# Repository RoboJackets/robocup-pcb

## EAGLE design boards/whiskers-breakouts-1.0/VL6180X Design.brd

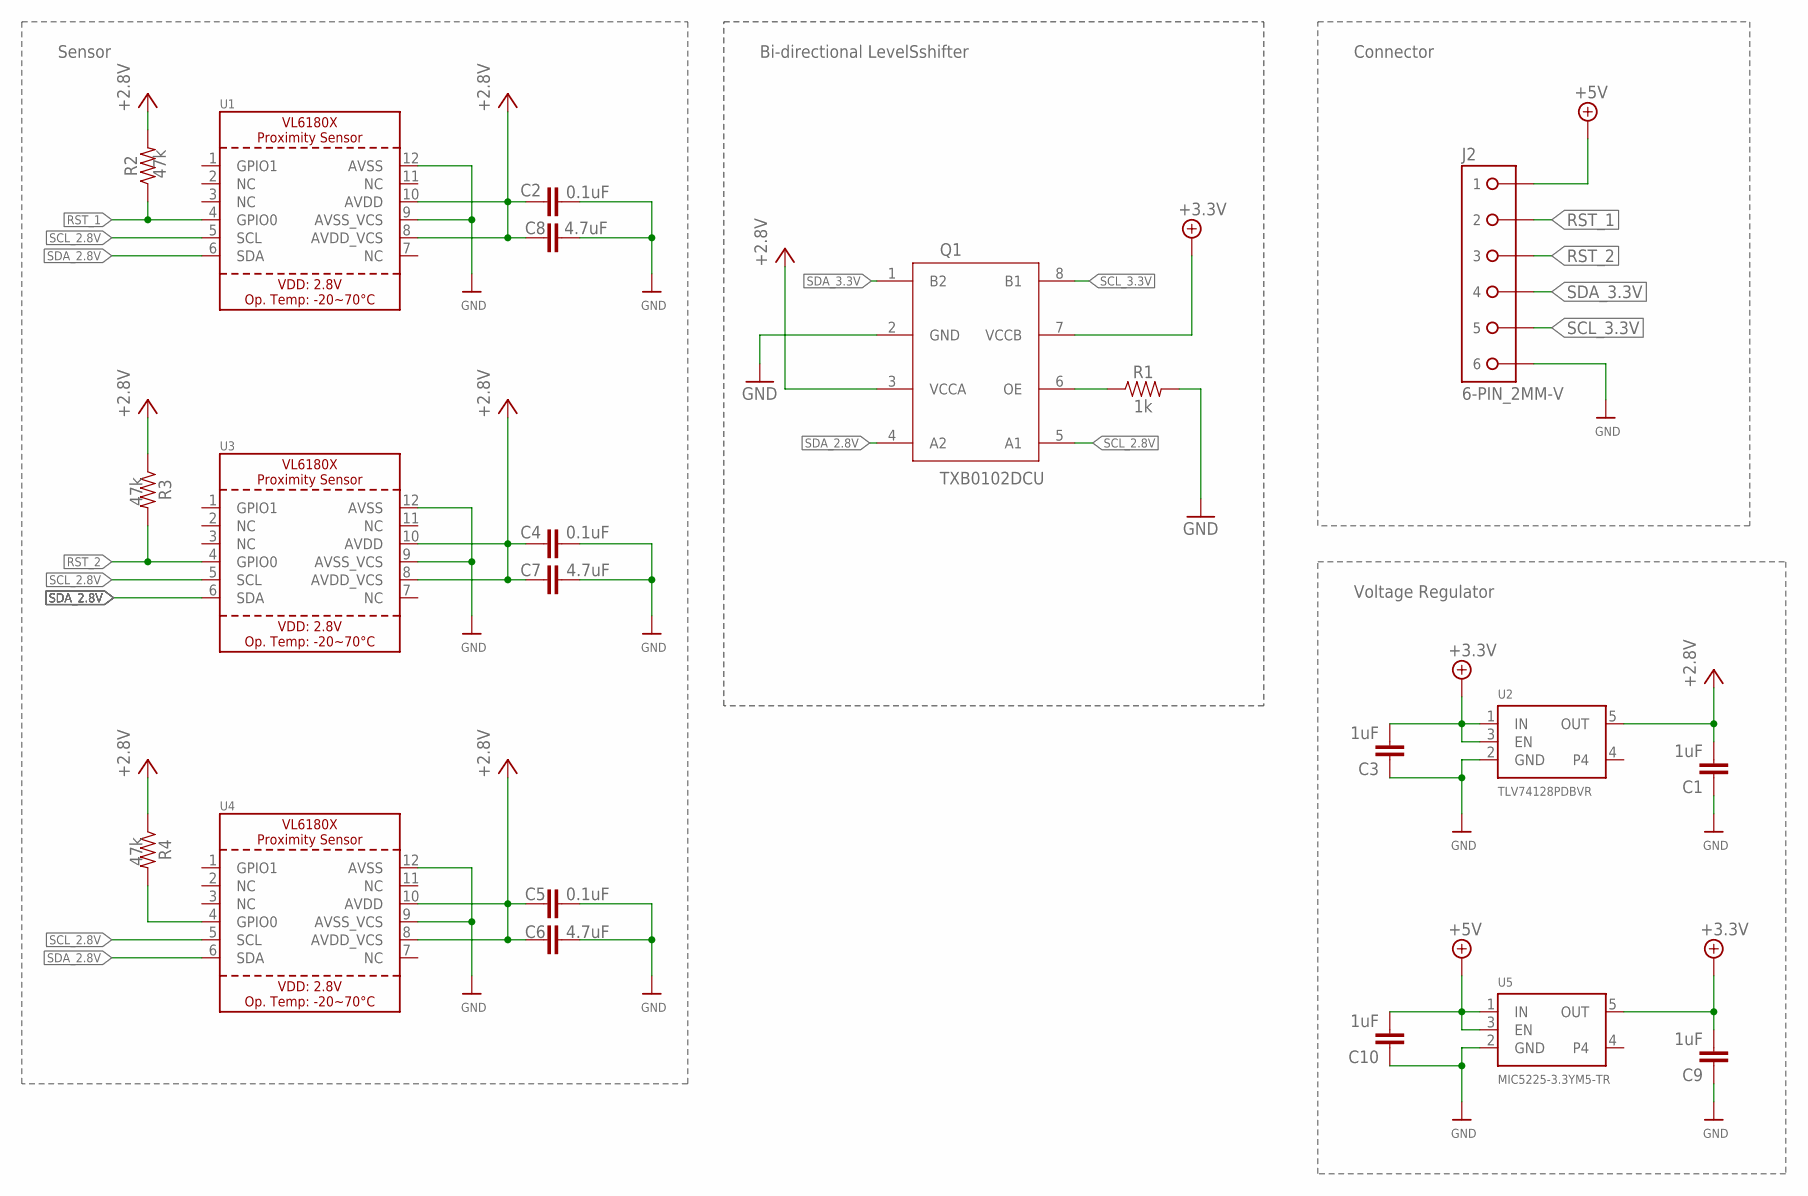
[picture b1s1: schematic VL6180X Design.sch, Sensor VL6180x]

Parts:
C1, C3, C9, C10: 1uF; 0603
C2, C4, C5: 0.1uF; 0603
C6, C7, C8: 4.7uF; 0603
J2: 6-PIN_2MM-V; 2MM-6-V
Q1: TXB0102DCU; VFSOP-8
R1: 1k; 0603
R2, R3, R4: 47k; 0603
U1, U3, U4: VL6180X; VL6180
U2: TLV74128PDBVR; SOT23-5
U5: MIC5225-3.3YM5-TR; SOT23-5

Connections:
+2.8V: C1.2, C2.1, C4.1, C5.1, C6.1, C7.1, C8.1, Q1.3 (VCCA), R2.2, R3.1, R4.1, U1.8 (AVDD_VCS), U1.10 (AVDD), U2.5 (OUT), U3.8 (AVDD_VCS), U3.10 (AVDD), U4.8 (AVDD_VCS), U4.10 (AVDD)
+3.3V: C3.2, C9.2, Q1.7 (VCCB), U2.1 (IN), U2.3 (EN), U5.5 (OUT)
+5V: C10.2, J2.1, U5.1 (IN), U5.3 (EN)
GND: C1.1, C2.2, C3.1, C4.2, C5.2, C6.2, C7.2, C8.2, C9.1, C10.1, J2.6, Q1.2 (GND), R1.2, U1.9 (AVSS_VCS), U1.12 (AVSS), U2.2 (GND), U3.9 (AVSS_VCS), U3.12 (AVSS), U4.9 (AVSS_VCS), U4.12 (AVSS), U5.2 (GND)
unnamed: Q1.6 (OE), R1.1
RST_1: J2.2, R2.1, U1.4 (GPIO0)
RST_2: J2.3, R3.2, U3.4 (GPIO0)
RST_3: R4.2, U4.4 (GPIO0)
SCL_2.8V: Q1.5 (A1), U1.5 (SCL), U3.5 (SCL), U4.5 (SCL)
SCL_3.3V: J2.5, Q1.8 (B1)
SDA_2.8V: Q1.4 (A2), U1.6 (SDA), U3.6 (SDA), U4.6 (SDA)
SDA_3.3V: J2.4, Q1.1 (B2)

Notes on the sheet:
Sensor
Connector
Bi-directional LevelSshifter
Voltage Regulator

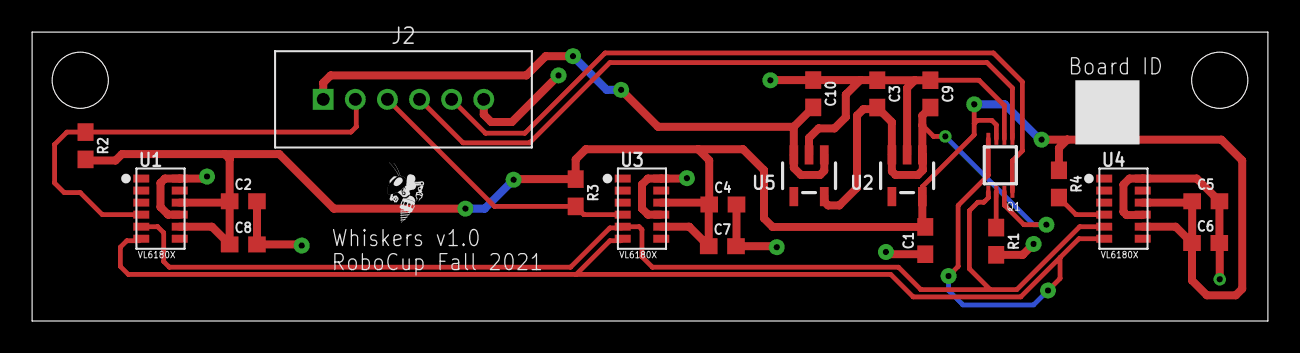
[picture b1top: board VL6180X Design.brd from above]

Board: 2 copper layers, 77.0 x 18.0 mm, 22 parts (0 on the bottom side), 12 nets.

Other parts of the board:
U$12: ROBOBUZZ_0.2X

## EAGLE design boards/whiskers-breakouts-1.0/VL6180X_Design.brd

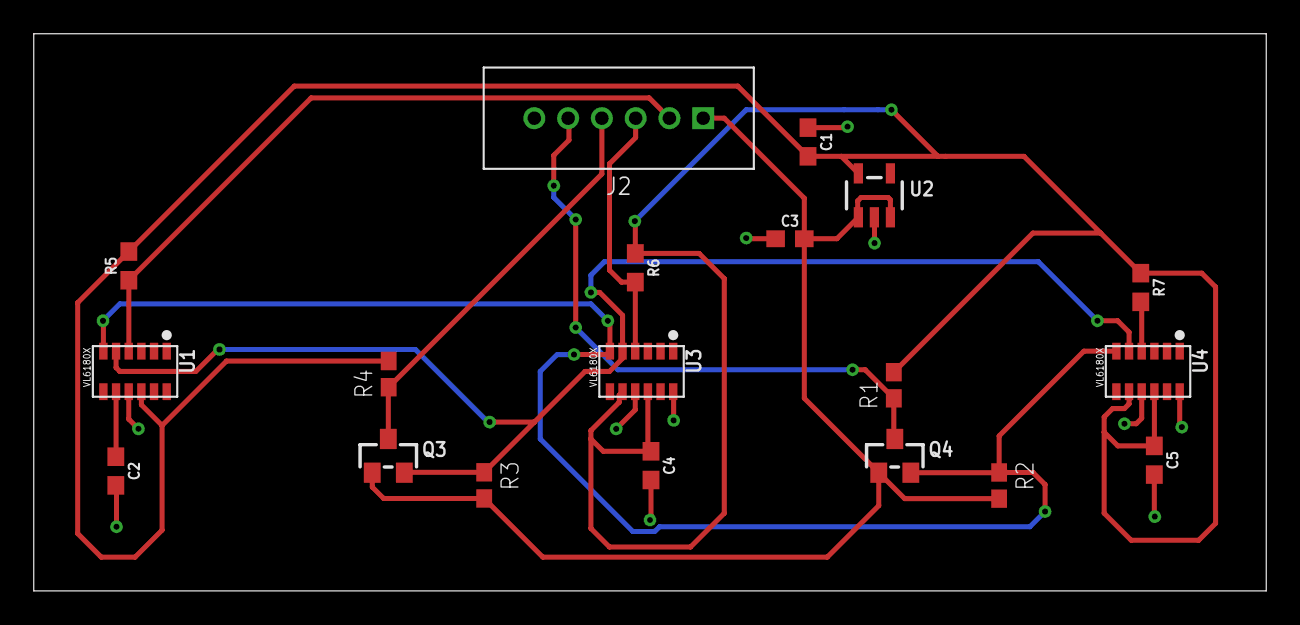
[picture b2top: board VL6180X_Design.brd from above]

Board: 2 copper layers, 73.0 x 33.0 mm, 19 parts (0 on the bottom side), 10 nets.

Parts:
C1, C3: 1uF; 0603
C2, C4, C5: 0.1uF; 0603
J2: 6-PIN_2MM-V; 2MM-6-V
Q3, Q4: BSS138; SOT23-WIDE
R1: 10k; R0603W
R2, R3, R4: 4.7k; R0603W
R5, R6, R7: 47k; 0603
U1, U3, U4: VL6180X; VL6180
U2: MIC5225_2.8V; SOT23-5

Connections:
+3.3V: C3.2, J2.1, Q3.1, Q4.1, R2.2, R3.2, U2.1, U2.3
GND: C1.1, C2.2, C3.1, C4.2, C5.2, J2.6, U1.9, U1.12, U2.2, U3.9, U3.12, U4.9, U4.12
RST_1: J2.2, R5.1, U1.4
RST_2: J2.3, R6.2, U3.4
RST_3: R7.2, U4.4
SCL_2.8V: Q3.2, R3.1, U1.5, U3.5, U4.5
SCL_3.3V: J2.4, Q3.3, R4.1
SDA_2.8V: Q4.2, R2.1, U1.6, U3.6, U4.6
SDA_3.3V: J2.5, Q4.3, R1.1
VCC: C1.2, C2.1, C4.1, C5.1, R1.2, R4.2, R5.2, R6.1, R7.1, U1.8, U1.10, U2.5, U3.8, U3.10, U4.8, U4.10

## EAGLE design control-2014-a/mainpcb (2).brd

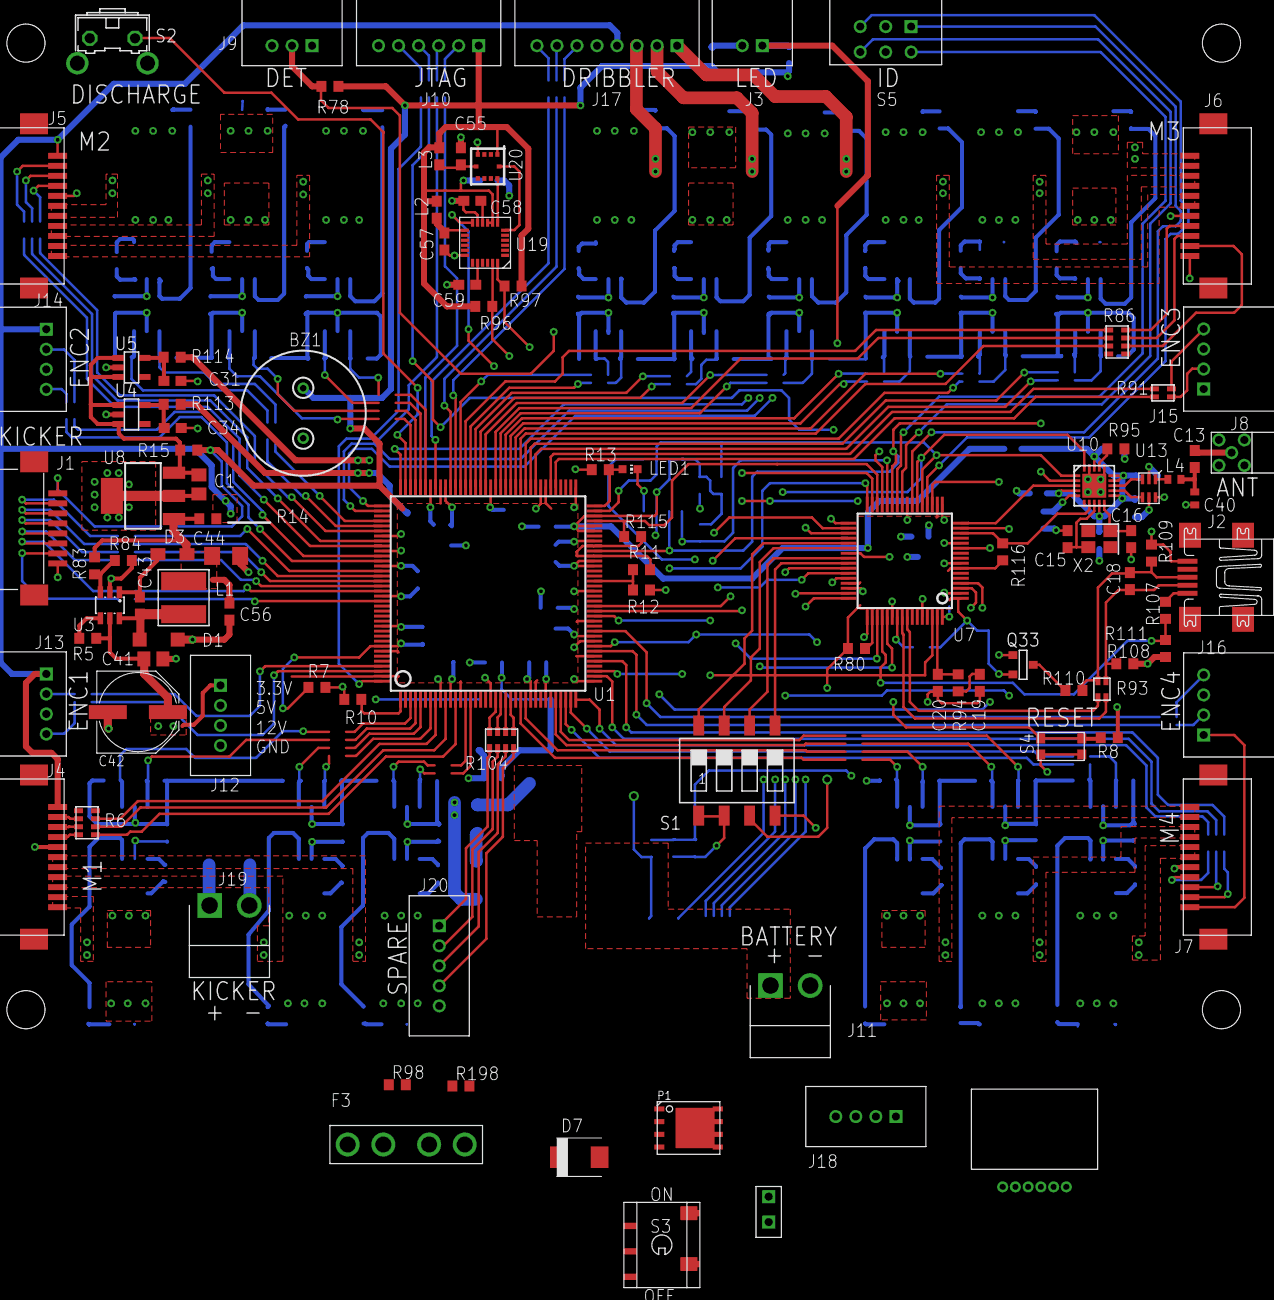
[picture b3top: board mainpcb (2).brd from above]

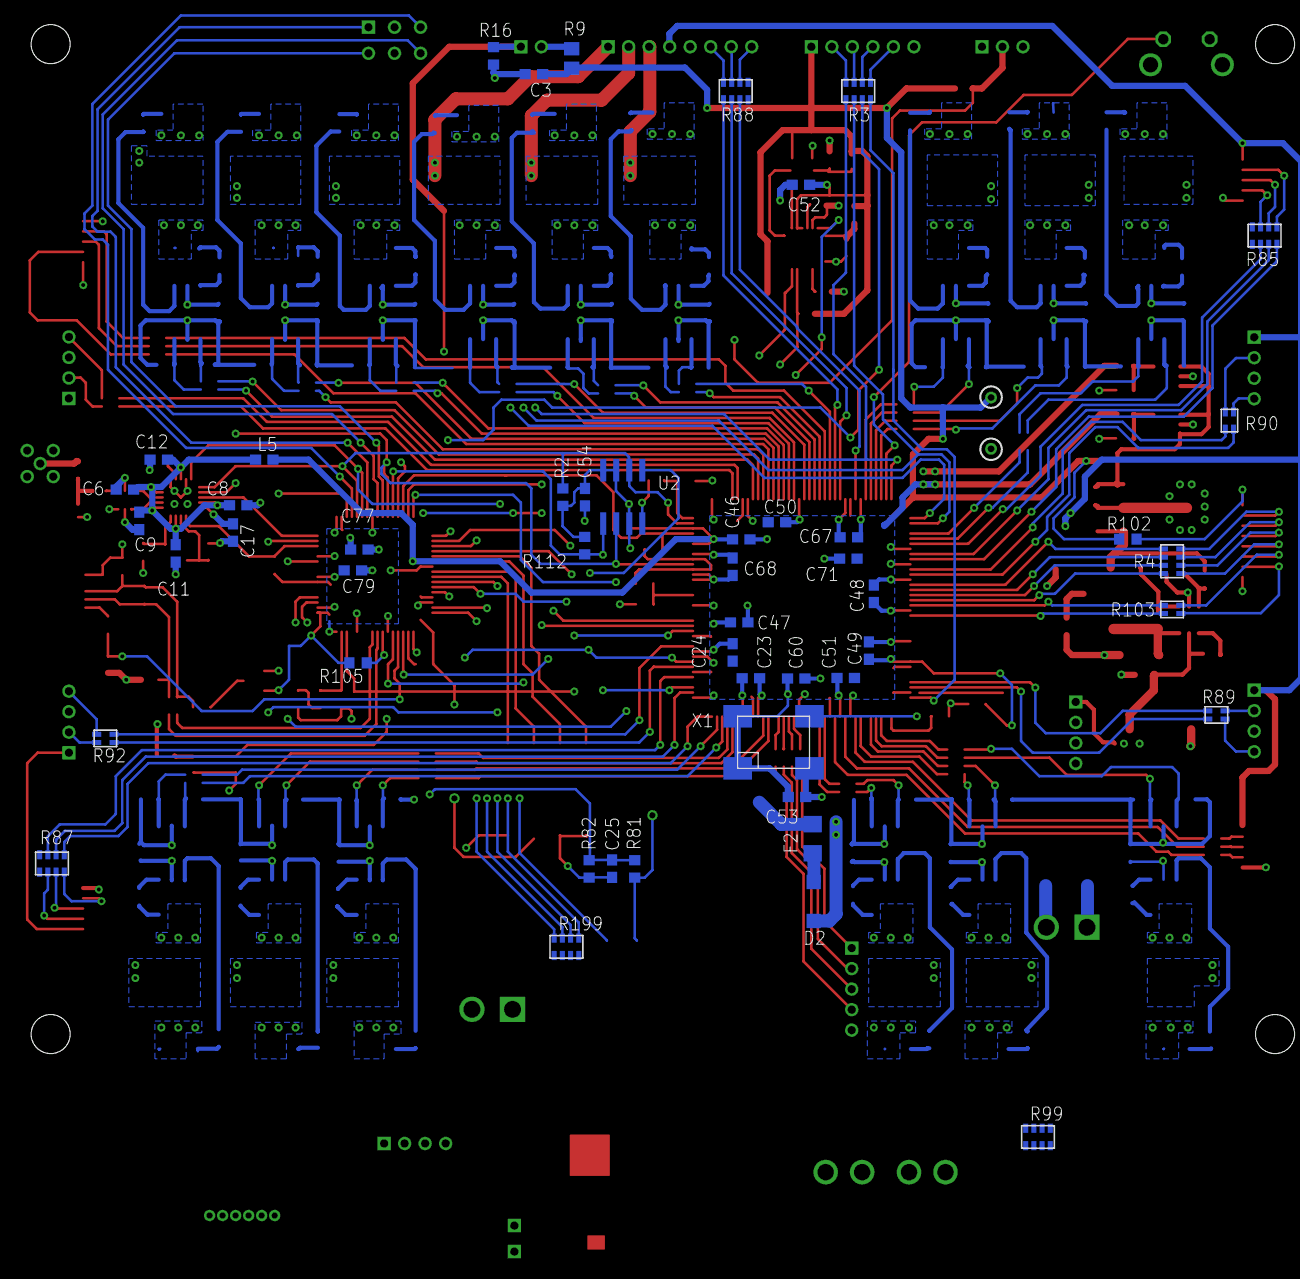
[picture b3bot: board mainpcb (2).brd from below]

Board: 4 copper layers, 151 parts (49 on the bottom side), 168 nets.

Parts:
BZ1: PS12
C1: 10uF; C0805
C3, C31, C34: 1uF; C0603
C6, C17, C23, C24, C25, C46, C47, C48, C49, C50, C51, C52, C53, C54, C55, C56, C57, C58, C60, C67, C68, C71, C77, C79: 100nF; C0603
C8, C11, C19, C43: 10nF; C0603
C9, C59: 2.2nF; C0603
C12: 220nF; C0603
C13: 100pF; C0603
C15, C16: 27pF; C0603
C18: 33pF; C0603
C20: 1nF; C0603
C40: 500R07S1R8BV4T; C0402
C41: 1uF 35V; C0805
C42: 100uF 25V; PANASONIC_E
C44: 22uF 6.3V; C1206
D1, D2: MBRX160-TP; SOD123
D3: BAS16H; SOD323-W
D7: SMBJP6KE18A-TP; SMBJ
F2: SF-1206F100-2; F1206
F3: 2x BK6011 [30A]; FUSE_MINI_ATC
J1: 0528520870
J2: MINI-USB; UX60A-MB-5ST
J3: 2MM-2H; 2MM-2-H
J4, J5, J6, J7: Molex 0522711179; FH_11_HOR
J8: MMCX_RA
J9: 2MM-3H; 2MM-3-H
J10: 2MM-6H; 2MM-6-H
J11: BATT; JST_VH_2_RA
J12, J18: 2MM-4V; 2MM-4-V
J13, J14, J15, J16: 2MM-4H; 2MM-4-H
J17: 2MM-8H; 2MM-8-H
J19: JST_VH_2; JST_VH_2_RA
J20: 2MM-5V; 2MM-5-V
L1: SDR0403-270KL; SDR0403
L2, L3, L5: HZ0603B102R-10; C0603
L4: L-07C5N6SV6T; R0402
LED1: CHIP-LED0603
LED2: 5350T5
LED7: LDS-M514RI-RA
P1: SI7141DP; POWERPAK_SO-8
Q33: FDV304P; SOT-23
R2, R5, R7, R8, R12, R82, R84, R96, R97, R111, R112, R116: 10.0k; R0603
R3, R4, R6, R85, R86, R87, R88, R99, R104, R199: 220; RA_4_1206
R9: 150 1/8W; R0805
R10, R13, R107, R198: 220; R0603
R11, R80, R105, R115: NP; R0603
R14, R15, R102, R113, R114: 0; R0603
R16: 100k; R0603
R78: 5.6k; R0603
R81: 68k; R0603
R83: 52.3k; R0603
R89, R90, R91, R92, R103: 220; RA_2_0606
R93: 27; RA_2_0606
R94, R110: 1.5k; R0603
R95: 56k; R0603
R98: 1k+; R0603
R108, R109: 330k; R0603
S1: SWS004; SMS-004
S2: B3F-31XX
S3: G3T12AP_SPDT; G3T12AP_SP
S4: KMR2
S5: 94HBB16RAT; HEX-RA-2C
U1: XC3S100E; TQFP144
U2: M25P10; SO08
U3: LM2734; SOT23-6L
U4: MCP1824T-1202E/OT; SOT23-5
U5: MCP1824T-2502E/OT; SOT23-5
U7: AT91SAM7S256; SQFP-S-10X10-64
U8: MCP1824ST-3302E/DB; SOT223
U10: CC1101; QLP20
U13: 0896BM15A0001
U19: IMU3000
U20: KXTF9-2050; KXTF9
X1: 18.432MHz; XTAL_LCC
X2: 644-1055-1-ND; XTAL-3.2X2.5

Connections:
12V_LOGIC: C41.1, C42.+, D2.C, J12.3, R5.2, U3.5
+1.2V: C24.1, C50.1, C51.1, C71.1, R113.1, U1.9, U1.45, U1.80, U1.115
+1.8V: C79.1, U7.8, U7.12, U7.24, U7.54, U7.64
+2.5V: BZ1.2, C3.1, C23.1, C46.1, C47.1, C48.1, C49.1, C52.1, C53.1, C54.1, C60.1, C67.1, C68.1, C77.1, J10.1, L2.1, L3.1, L5.1, Q33.2, R2.2, R7.1, R8.2, R9.1, R11.2, R13.1, R15.2, R78.1, R80.2, R96.2, R97.2, R102.1, R105.2, R112.2, R114.1, R115.2, R116.2, U1.13, U1.28, U1.30, U1.42, U1.49, U1.62, U1.64, U1.65, U1.67, U1.68, U1.70, U1.79, U1.100, U1.102, U1.121, U1.137, U1.138, U1.143, U2.3, U2.7, U2.8, U7.1, U7.7, U7.18, U7.45, U7.58, U7.59, U19.8, U19.9, U20.1, X1.1, X1.4
+5V: J4.11, J5.11, J6.11, J7.11, J12.2, J13.1, J14.1, J15.1, J16.1, J17.4, R14.2
+12V: F3.3, F3.4, J19.1, R81.2
/CONNECT: Q33.3, U7.19
ARM_TDI: U1.109, U7.33
ARM_TDO: R3.5, U7.49
BALL_DET: J9.2, R78.2, U7.3
BALL_LED: J3.1, R16.1, U7.44
BATT_SENSE: C25.1, R81.1, R82.2, U7.4
BUZZ: BZ1.1, U7.32
DDM: R93.2, U7.56
DDP: R93.4, U7.57
DISCHARGE: S2.1, U1.107
DONE: LED1.A, R13.2, U1.72
DP1: S1.8, U7.37
DP2: S1.7, U7.38
DP4: S1.5, U7.41
FLASH_NCS: R112.1, U1.39, U2.1, U7.28
FPGA_NCS: R115.1, U1.69, U7.30
FPGA_SPARE_0: R104.2, U1.20
FPGA_SPARE_1: R104.4, U1.21
FPGA_SPARE_2: R104.6, U1.22
FPGA_SPARE_3: R104.8, U1.23
FPGA_TDI: R3.7, U1.144
FS0: U1.52, U7.31
FS1: U1.51, U7.29
GND: C1.2, C3.2, C6.2, C8.2, C9.2, C11.2, C12.2, C15.2, C16.2, C17.2, C19.2, C20.2, C23.2, C24.2, C25.2, C31.2, C34.2, C40.2, C41.2, C42.-, C44.2, C46.2, C47.2, C48.2, C49.2, C50.2, C51.2, C52.2, C53.2, C54.2, C55.2, C56.2, C57.2, C58.2, C59.2, C60.2, C67.2, C68.2, C71.2, C77.2, C79.2, D1.A, J1.8, J2.5, J4.7, J5.7, J6.7, J7.7, J8.P$2, J8.P$3, J8.P$4, J8.P$5, J9.1, J10.6, J11.2, J12.4, J13.3, J14.3, J15.3, J16.3, J17.5, J19.2, J20.5, LED1.C, R12.1, R16.2, R82.1, R84.1, R95.1, R108.1, R109.1, R111.1, S1.1, S1.2, S1.4, S2.2, S4.1, S4.3, S5.C1, S5.C2, U1.11, U1.19, U1.27, U1.37, U1.46, U1.55, U1.60, U1.61, U1.73, U1.90, U1.99, U1.118, U1.127, U1.133, U2.4, U3.2, U4.2, U5.2, U7.2, U7.17, U7.46, U7.60, U8.2, U8.4, U10.16, U10.19, U10.DAP, U13.2, U13.5, U13.6, U19.11, U19.18, U20.4, X1.2
I2C_SCL: R96.1, U7.36, U19.23
I2C_SDA: R97.1, U7.43, U19.24
ID0: S5.1, U7.23
ID1: S5.2, U7.25
ID2: S5.4, U7.20
ID3: S5.8, U7.26
IMU_INT: U7.34, U19.12
KCHARGE: R4.2, U1.125
KCHIP: R103.3, U1.128
KDONE: R4.4, U1.124
KKICK: R103.1, U1.126
KSCL: R4.6, U1.123
KSDA: R4.8, U1.122
LED_LR: R199.8, U7.35
LED_RG: R199.2, U7.48
LED_RR: R199.4, U7.47
LED_RY: R199.6, U7.15
M1A: J4.1, J4.2
M1B: J4.3, J4.4
M1C: J4.5, J4.6
M1ENC_A: R89.1, U1.141
M1ENC_B: R89.3, U1.142
M1HALL_A: R6.3, U1.10
M1HALL_B: R6.1, U1.12
M1HALL_C: R6.5, U1.8
M2: R11.1, R12.2, U1.57
M2A: J5.1, J5.2
M2B: J5.3, J5.4
M2C: J5.5, J5.6
M2ENC_A: R90.1, U1.119
M2ENC_B: R90.3, U1.120
M2HALL_A: R85.5, U1.116
M2HALL_B: R85.3, U1.114
M2HALL_C: R85.7, U1.117
M3A: J6.1, J6.2
M3B: J6.3, J6.4
M3C: J6.5, J6.6
M3ENC_A: R91.2, U1.77
M3ENC_B: R91.4, U1.78
M3HALL_A: R86.3, U1.89
M3HALL_B: R86.1, U1.95
M3HALL_C: R86.5, U1.84
M4A: J7.1, J7.2
M4B: J7.3, J7.4
M4C: J7.5, J7.6
M4ENC_A: R92.1, U1.43
M4ENC_B: R92.3, U1.47
M4HALL_A: R87.3, U1.38
M4HALL_B: R87.1, U1.36
M4HALL_C: R87.5, U1.41
M5HALL_A: R88.1, U1.97
M5HALL_B: R88.3, U1.98
M5HALL_C: R88.5, U1.101
MCU_PROGB: R7.2, R10.1, U7.11
MISO: U1.63, U2.2, U7.27, U10.2
MOSI: U1.44, U2.5, U7.22, U10.20
unnamed: J13.4, R89.4
unnamed: J10.3, R3.4
unnamed: J10.5, R3.8
unnamed: C44.1, C56.1, D3.A, L1.2, R14.1, R83.2, U8.1
unnamed: J17.6, R88.2
unnamed: C1.1, R15.1, U4.1, U4.3, U5.1, U5.3, U8.3
unnamed: J3.2, R9.2
unnamed: C43.2, D1.C, L1.1, U3.6
unnamed: J4.8, R6.2
unnamed: J4.9, R6.4
unnamed: J4.10, R6.6
unnamed: J5.8, R85.4
unnamed: J5.10, R85.8
unnamed: J5.9, R85.6
unnamed: J6.8, R86.2
unnamed: J6.10, R86.6
unnamed: J6.9, R86.4
unnamed: J7.8, R87.2
unnamed: J7.10, R87.6
unnamed: J7.9, R87.4
unnamed: J17.7, R88.4
unnamed: J17.8, R88.6
unnamed: C55.1, L3.2, U20.5
unnamed: J1.2, R4.7
unnamed: C34.1, R113.2, U4.5
unnamed: C31.1, R114.2, U5.5
unnamed: R80.1, U7.50
unnamed: C18.2, J2.2, R93.1, R108.2
unnamed: J1.3, R4.5
unnamed: J1.4, R4.3
unnamed: R5.1, U3.4
unnamed: U19.7, U20.9
unnamed: C43.1, D3.C, U3.1
unnamed: J1.5, R4.1
unnamed: R83.1, R84.2, U3.3
unnamed: J10.4, R3.6
unnamed: R105.1, U7.55
unnamed: J10.2, R3.2
unnamed: C18.1, J2.3, R93.3, R109.2, R110.1
unnamed: Q33.1, R110.2
unnamed: C19.1, R94.1
unnamed: C20.1, R94.2, U7.63
unnamed: D2.A, F2.2
unnamed: J13.2, R89.2
unnamed: J16.4, R92.4
unnamed: J16.2, R92.2
unnamed: J15.4, R91.3
unnamed: J15.2, R91.1
unnamed: J14.4, R90.4
unnamed: J14.2, R90.2
unnamed: U19.6, U20.10
unnamed: C57.1, L2.2, U19.13
unnamed: C58.1, U19.10
unnamed: C59.1, U19.20
unnamed: J1.6, R103.2
unnamed: J1.7, R103.4
unnamed: J1.1, R102.2
unnamed: C17.1, U10.5
unnamed: R95.2, U10.17
unnamed: C16.1, U10.10, X2.1
unnamed: J20.3, R104.5
unnamed: J20.2, R104.3
unnamed: J20.1, R104.1
unnamed: J20.4, R104.7
unnamed: C15.1, U10.8, X2.3
unnamed: L4.1, U13.1
unnamed: C13.1, C40.1, L4.2
unnamed: J2.1, R107.2
unnamed: U10.12, U13.4
unnamed: U10.13, U13.3
unnamed: C13.2, J8.P$1
PROGB: R10.2, U1.1
RADIO_INT: U7.16, U10.3
RADIO_NCS: R116.1, U7.14, U10.7
RADIO_VDD: C6.1, C8.1, C9.1, C11.1, C12.1, L5.2, U10.4, U10.9, U10.11, U10.14, U10.15, U10.18
SCK: R2.1, U1.71, U2.6, U7.21, U10.1
SRST: R8.1, S4.2, S4.4, U7.39
SYSCLK: U1.50, U7.62, X1.3
TCK: R3.3, U1.110, U7.53
TMS: R3.1, U1.108, U7.51
TST: S1.6, U7.40
VBUS: R107.1, R111.2, U7.52

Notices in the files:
parts and their libraries:
microbuilder: This work is placed in the public domain, and may be freely used for commercial and non-commercial work with the following conditions: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
SparkFun-Capacitors: Licensing: Creative Commons ShareAlike 4.0 International - https://creativecommons.org/licenses/by-sa/4.0
